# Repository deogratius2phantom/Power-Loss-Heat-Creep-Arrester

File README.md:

# Power Loss Heat Creep Arrester

A KiCad PCB design for a timer circuit that provides **24 V backup power to a 3D printer hotend fan** in the event of a power loss during printing. This prevents heat creep — the condition where residual heat travels up into the heatsink passage, causing filament to swell, clog, or jam.

---

## Overview

When a 3D printer loses power mid-print, the hotend heater turns off but residual heat remains in the heater block. Without the cooling fan running, this heat can creep up the cold zone, softening and swelling the filament inside the heatsink passage. The result is a jam that requires manual disassembly to clear.

This circuit detects the power loss event and uses a backup energy source (e.g. a capacitor bank or small battery) to keep the hotend fan spinning for a timed period — long enough for the heat to dissipate safely.

---

## Features

- Detects main power loss and triggers a timed backup fan drive
- Designed to supply 24 V to a standard 3D printer part-cooling or hotend fan
- Powered by a **Nokia BL-5C 3.7 V Li-ion battery** — widely available, compact, and plug-in replaceable
- Compact PCB footprint suitable for mounting inside a printer enclosure
- Fully open hardware (CC0 1.0 Universal licence)

---

## Board Preview

**Front (component side)**

**Back — rev_1.0 silkscreen**

The back silkscreen includes:
- **XundaTech / Heat Creep Arrester V1.0** — product branding
- **QR code** — scan to open this GitHub repository directly from the physical board
- **Connector pinout labels** (`FAN 24V`, `FAN GND`, `TO`, `GND`) — printed next to J3 for field assembly without needing a datasheet

📄 Full schematic & layout documentation: [PowerLossHeatCreepArrester.pdf](docs/PowerLossHeatCreepArrester.pdf)

---

## Repository Structure

```
Power-Loss-Heat-Creep-Arrester/
├── PowerLossHeatCreepArrester_v1.0/                      # KiCad v1.0 project (main design)
│   ├── PowerLossHeatCreepArrester_v1.0.kicad_pro         # KiCad project file
│   ├── PowerLossHeatCreepArrester_v1.0.kicad_sch         # Schematic
│   ├── PowerLossHeatCreepArrester_v1.0.kicad_pcb         # PCB layout
│   ├── board_v1.step                                     # 3D board export (v1)
│   ├── board_v11.step                                    # 3D board export (v11)
│   ├── .step                                             # Additional 3D export
│   ├── fabrication-toolkit-options.json                  # KiCad fabrication toolkit config
│   ├── bom/                                              # Bill of Materials & assembly aids
│   │   └── manual_assembly_ibom.html                    # Interactive BOM for manual assembly
│   └── production/                                       # Ready-to-order production files
│       ├── PowerLossHeatCreepArrester_v1.0.zip           # Gerber bundle for PCB fab
│       ├── bom.csv                                       # Bill of Materials
│       ├── designators.csv                               # Component designators
│       ├── netlist.ipc                                   # IPC netlist
│       └── positions.csv                                 # Pick-and-place positions
├── libraries/
│   └── PowerLossHeatCreepArrester.kicad_sym              # Custom schematic symbols
├── footprints/
│   └── PowerLossHeatCreepArrester.pretty/                # Custom PCB footprints
├── fabrication/
│   ├── gerbers/                                          # Gerber files for PCB manufacture
│   └── bom/                                             # Bill of Materials exports
├── docs/                                                 # Documentation & board images
│   ├── PowerLossHeatCreepArrester.pdf                   # Full schematic & layout PDF
│   ├── Screenshot 2026-06-02 at 18.37.28.png            # Board front view
│   └── Screenshot 2026-06-02 at 18.37.43.png            # Board back view
├── Heat Creep Arrester.pdf                               # Project overview document
├── .gitignore
├── LICENSE
└── README.md
```

---

## Getting Started

### Prerequisites

- [KiCad 7 or later](https://www.kicad.org/download/) (the project files use the KiCad 6+ S-expression format)

### Opening the Project

1. Clone or download this repository.
2. Open KiCad and select **File → Open Project**.
3. Navigate to `PowerLossHeatCreepArrester_v1.0/` and open `PowerLossHeatCreepArrester_v1.0.kicad_pro`.
4. The schematic (`*.kicad_sch`) and PCB layout (`*.kicad_pcb`) will be available from the KiCad project manager.

### Generating Fabrication Files

### Interactive BOM (Manual Assembly)

Open the interactive BOM directly in your browser — no setup needed:

**🔗 [View Interactive BOM online](https://htmlpreview.github.io/?https://github.com/deogratius2phantom/Power-Loss-Heat-Creep-Arrester/blob/main/PowerLossHeatCreepArrester_v1.0/bom/manual_assembly_ibom.html)**

Or open the file locally: `PowerLossHeatCreepArrester_v1.0/bom/manual_assembly_ibom.html`

It provides an interactive board view where you can click each component to highlight its placement — ideal for hand-soldering.

### Production Files

Ready-to-order files are in `PowerLossHeatCreepArrester_v1.0/production/`:

| File | Description |
|------|-------------|
| `PowerLossHeatCreepArrester_v1.0.zip` | Gerber bundle — upload directly to your PCB fab |
| `bom.csv` | Bill of Materials |
| `designators.csv` | Component designator mapping |
| `netlist.ipc` | IPC-D-356 netlist |
| `positions.csv` | Pick-and-place positions for SMT assembly |

To regenerate from source in KiCad PCB Editor (`pcbnew`):

1. Go to **File → Fabrication Outputs → Gerbers** → output to `fabrication/gerbers/`.
2. Generate the drill file via **File → Fabrication Outputs → Drill Files**.
3. Export the BOM via **File → Fabrication Outputs → BOM** → output to `fabrication/bom/`.

---

## Design Notes

| Parameter | Value |
|-----------|-------|
| Supply voltage | 24 V |
| Target load | Hotend / part-cooling fan |
| Fan activation | Only when hotend > 50 °C (adjustable via RV1) |
| Temperature sensing | Independent thermistor circuit (U4) — separate from printer NTC |
| PCB layers | 2 |
| Board thickness | 1.6 mm |
| Solder mask clearance | 0.005 mm |

---

## Revision History

### rev_1.0 (current branch)

Key changes from initial commit:

- **Independent temperature monitoring (U4 added):** A dedicated temperature sensing IC with its own thermistor was added after determining it is not feasible to share the printer's NTC across both the printer control board and this backup supply board without a carefully designed 3.3 V interface. U4 provides a clean, isolated temperature signal to LM393 comparator 2.
- **Comparator voltage divider recalculated:** R15 `210k → 52.3k`, R16 `40.2k → 10k` — revised to correctly set the 24 V power-loss detection threshold.
- **Hysteresis / reference network updated:** R21 `200k → 100k`, plus two comparator reference resistors adjusted (`10k → 47k` and `10k → 910k`) to match the new divider ratios.
- **GND symbol rerouted and thermistor label repositioned** on the schematic for clarity.
- **Net label typo fixed:** `indipendent_3d printer fan control input` → `independent_3d printer fan control input`.
- **PCB layout updated:** U4 placed at (138.51, 88.06), net assignments updated to match schematic changes, solder mask clearance set to 0.005 mm.
- **Back silkscreen additions:**
  - Product branding: `XundaTech / Heat Creep Arrester V1.0`
  - QR code linking to this GitHub repository (centre-back)
  - Connector pinout labels beside J3: `FAN 24V`, `FAN GND`, `TO`, `GND`

---

## Documentation

Full project documentation is in the [**GitHub Wiki**](https://github.com/deogratius2phantom/Power-Loss-Heat-Creep-Arrester/wiki):

| Wiki Page | Contents |
|-----------|----------|
| [Design Rationale](https://github.com/deogratius2phantom/Power-Loss-Heat-Creep-Arrester/wiki/Design-Rationale) | Why BL-5C, MT3608, TP4056, LM393 were chosen |
| [Circuit Theory](https://github.com/deogratius2phantom/Power-Loss-Heat-Creep-Arrester/wiki/Circuit-Theory) | How each circuit block works |
| [Bill of Materials & Sourcing](https://github.com/deogratius2phantom/Power-Loss-Heat-Creep-Arrester/wiki/Bill-of-Materials-and-Sourcing) | Full component list with supplier links |
| [Assembly Guide](https://github.com/deogratius2phantom/Power-Loss-Heat-Creep-Arrester/wiki/Assembly-Guide) | Step-by-step soldering instructions |
| [Testing & Calibration](https://github.com/deogratius2phantom/Power-Loss-Heat-Creep-Arrester/wiki/Testing-and-Calibration) | Verifying and tuning the circuit |
| [Troubleshooting](https://github.com/deogratius2phantom/Power-Loss-Heat-Creep-Arrester/wiki/Troubleshooting) | Common issues and fixes |
| [Version History](https://github.com/deogratius2phantom/Power-Loss-Heat-Creep-Arrester/wiki/Version-History) | Board revision log |

---

## Contributing

Contributions are welcome. See the [Contributing wiki page](https://github.com/deogratius2phantom/Power-Loss-Heat-Creep-Arrester/wiki/Contributing) for the full workflow. Please open an issue to discuss changes before submitting a pull request.

---

## Licence

This project is released into the public domain under the [CC0 1.0 Universal](LICENSE) licence. You are free to use, modify, and distribute this design without restriction.

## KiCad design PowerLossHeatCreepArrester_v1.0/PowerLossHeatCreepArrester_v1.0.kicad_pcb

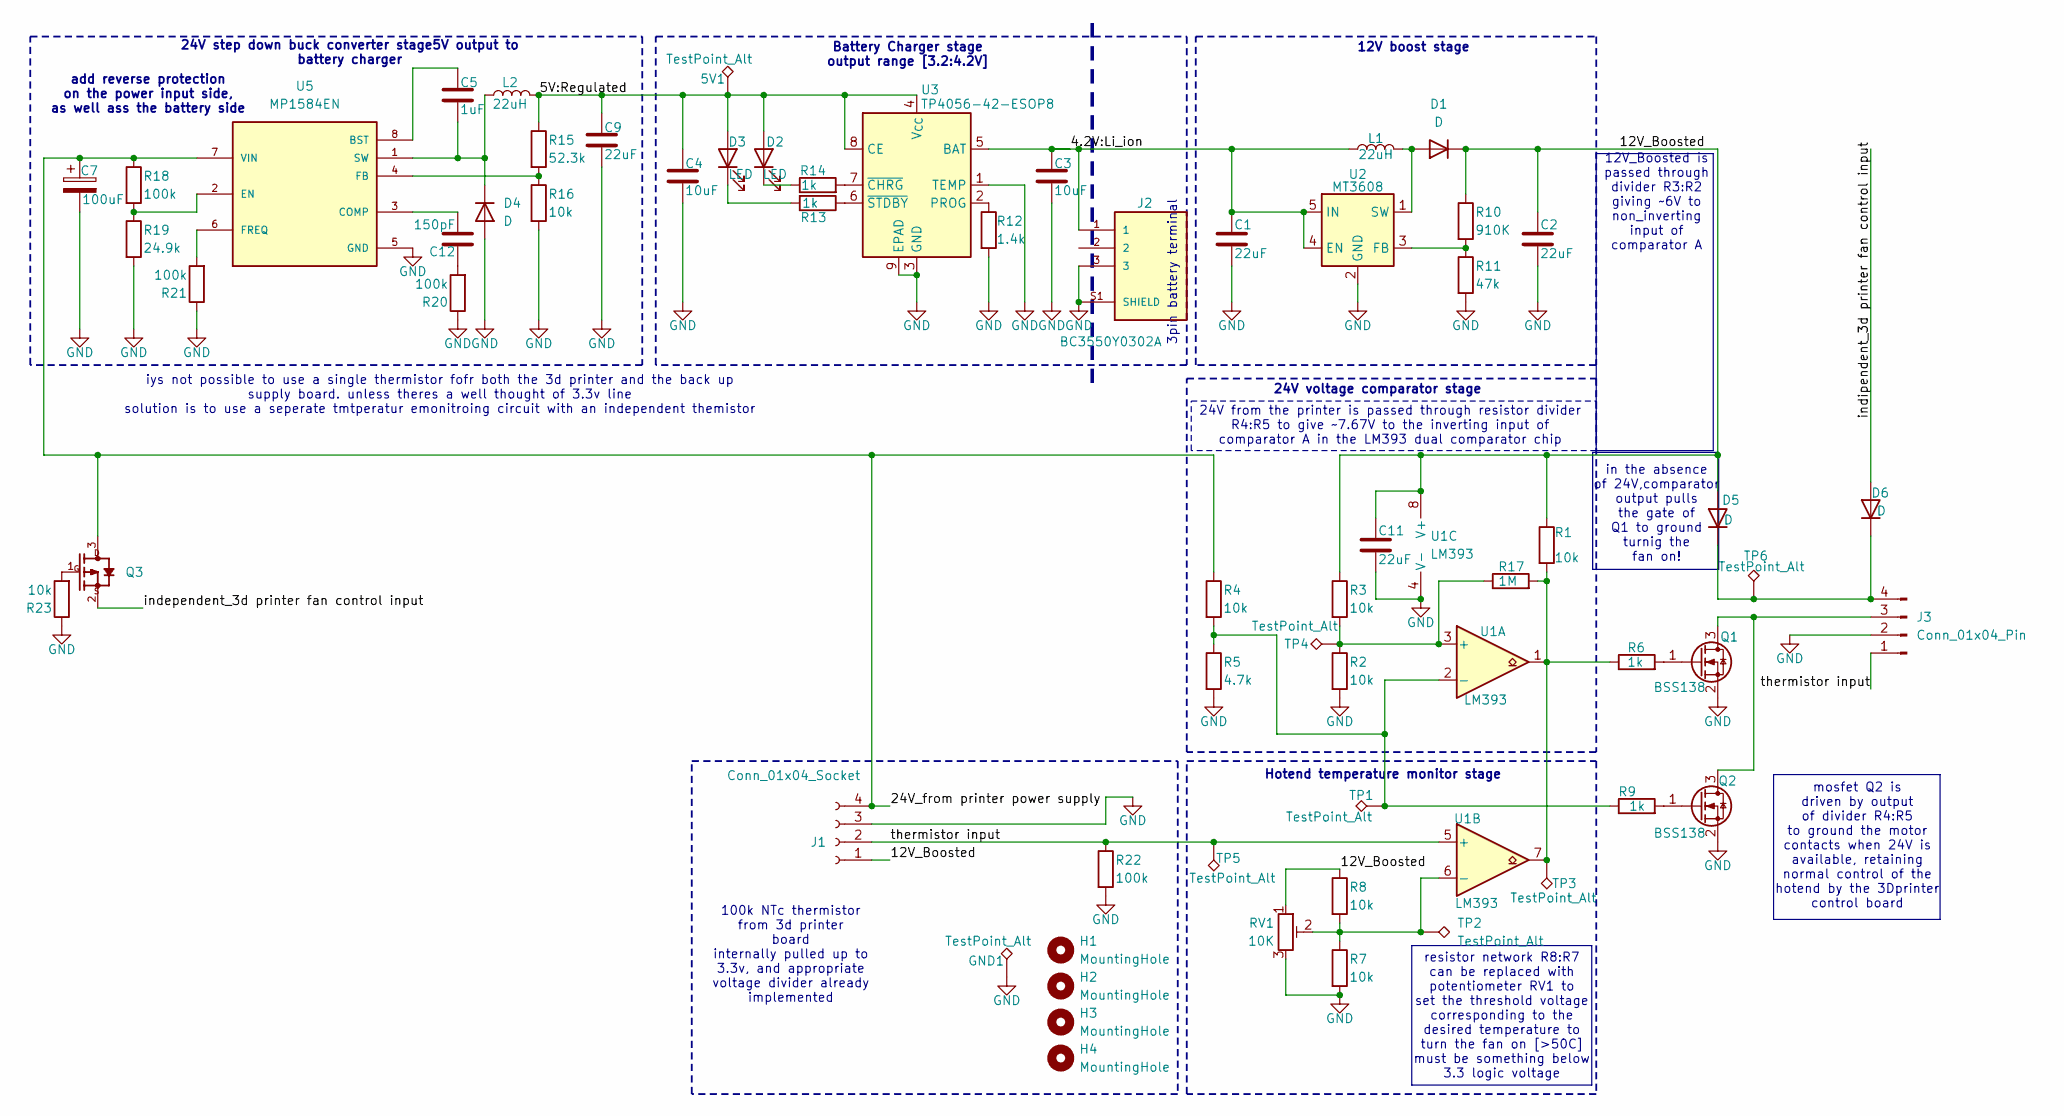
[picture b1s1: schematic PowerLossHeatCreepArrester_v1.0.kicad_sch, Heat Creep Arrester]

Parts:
5V1: TestPoint_Alt; TestPoint_Pad_D1.5mm
C1, C9: 22uF; C_0805_2012Metric
C2, C11: 22uF; C_0603_1608Metric
C3, C4: 10uF; C_0805_2012Metric
C5: 1uF; C_0805_2012Metric
C7: 100uF; CP_Radial_D5.0mm_P2.50mm
C12: 150pF; C_0603_1608Metric
D1, D4, D5, D6: D; D_SMA
D2, D3: LED; LED_0603_1608Metric
GND1: TestPoint_Alt; TestPoint_Pad_D1.5mm
H1, H2, H3, H4: MountingHole; MountingHole_3.2mm_M3_Pad
J1: Conn_01x04_Socket; PinHeader_1x04_P2.54mm_Vertical
J2: BC3550Y0302A; AMPHENOL_BC3550Y0302A; PARTREV 4
J3: Conn_01x04_Pin; PinHeader_1x04_P2.54mm_Vertical
L1, L2: 22uH; L_10.4x10.4_H4.8
Q1, Q2: BSS138; SOT-23
Q3: ZXMP6A13FTA; SOT-23; MPN ZXMP6A13FTA
R1, R2, R3, R4, R7, R8, R16, R23: 10k; R_0603_1608Metric
R5: 4.7k; R_0603_1608Metric
R6, R9, R13, R14: 1k; R_0603_1608Metric
R10: 910K; R_0603_1608Metric
R11: 47k; R_0603_1608Metric
R12: 1.4k; R_0603_1608Metric
R15: 52.3k; R_0603_1608Metric
R17: 1M; R_0603_1608Metric
R18, R20, R21, R22: 100k; R_0603_1608Metric
R19: 24.9k; R_0603_1608Metric
RV1: 10K; Potentiometer_ACP_CA14-VSMD_Vertical
TP1, TP2, TP3, TP4, TP5, TP6: TestPoint_Alt; TestPoint_Pad_D1.5mm
U1: LM393; SOIC-8_3.9x4.9mm_P1.27mm
U2: MT3608; SOT-23-6
U3: TP4056-42-ESOP8; SOIC-8-1EP_3.9x4.9mm_P1.27mm_EP2.41x3.3mm_ThermalVias
U5: MP1584EN; SOIC127P600X170-9N

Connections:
/4.2V:Li_ion: C1.1, C3.1, J2.1, L1.1, U2.4 (EN), U2.5 (IN), U3.5 (BAT)
/5V:Regulated: 5V1.1 (1_1), C4.1, C9.1, D2.2 (A), D3.2 (A), L2.2, R15.1, U3.4 (V_{CC}), U3.8 (CE)
/12V_Boosted: C2.1, C11.1, D1.1 (K), D5.2 (A), J1.1, R1.1, R3.1, R8.1, R10.1, RV1.1, U1.8 (V+)
/24V_from printer power supply: C7.1, J1.4, Q3.3, R4.1, R18.1, U5.7 (VIN)
/indipendent_3d printer fan control input: D6.2 (A)
/thermistor input: J1.2, J3.1, R22.1, TP5.1 (1_1), U1.5 (+)
GND: C1.2, C2.2, C3.2, C4.2, C7.2, C9.2, C11.2, D4.2 (A), GND1.1 (1_1), J1.3, J2.3, J2.S1 (SHIELD), J3.2, Q1.2 (S), Q2.2 (S), R2.2, R5.2, R7.2, R11.2, R12.2, R16.2, R19.2, R20.1, R21.1, R22.2, R23.1, RV1.3, U1.4 (V-), U2.2 (GND), U3.1 (TEMP), U3.3 (GND), U3.9 (EPAD), U5.5 (GND), U5.9 (GND)
unnamed: C12.1, R20.2
unnamed: D1.2 (A), L1.2, U2.1 (SW)
unnamed: D2.1 (K), R14.1
unnamed: D3.1 (K), R13.2
unnamed: C5.2, D4.1 (K), L2.1, U5.1 (SW)
unnamed: D5.1 (K), D6.1 (K), J3.4, TP6.1 (1_1)
unnamed: J3.3, Q1.3 (D), Q2.3 (D)
unnamed: Q1.1 (G), R6.2
unnamed: Q2.1 (G), R9.2
unnamed: Q3.1, R23.2
unnamed: R1.2, R6.1, R17.2, TP3.1 (1_1), U1.1, U1.7
unnamed: R2.1, R3.2, R17.1, TP4.1 (1_1), U1.3 (+)
unnamed: R4.2, R5.1, R9.1, TP1.1 (1_1), U1.2 (-)
unnamed: R7.1, R8.2, RV1.2, TP2.1, U1.6 (-)
unnamed: R10.2, R11.1, U2.3 (FB)
unnamed: R12.1, U3.2 (PROG)
unnamed: R14.2, U3.7 (~CHRG)
unnamed: R13.1, U3.6 (~STDBY)
unnamed: C5.1, U5.8 (BST)
unnamed: C12.2, U5.3 (COMP)
unnamed: R18.2, R19.1, U5.2 (EN)
unnamed: R15.2, R16.1, U5.4 (FB)
unnamed: R21.2, U5.6 (FREQ)

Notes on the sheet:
24V from the printer is passed through resistor divider R4:R5 to give ~7.67V to the inverting input of comparator A in the LM393 dual comparator chip
24V voltage comparator stage
Hotend temperature monitor stage
iys not possible to use a single thermistor fofr both the 3d printer and the back up supply board. unless theres a well thought of 3.3v line solution is to use a seperate tmtperatur emonitroing circuit with an independent themistor
add reverse protection on the power input side, as well ass the battery side
3pin battery terminal
Battery Charger stage output range [3.2:4.2V]
in the absence of 24V,comparator output pulls the gate of Q1 to ground turnig the fan on!
100k NTc thermistor from 3d printer board internally pulled up to 3.3v, and appropriate voltage divider already implemented
12V boost stage
resistor network R8:R7 can be replaced with potentiometer RV1 to set the threshold voltage corresponding to the desired temperature to turn the fan on [>50C] must be something below 3.3 logic voltage
12V_Boosted is passed through divider R3:R2 giving ~6V to non_inverting input of comparator A
24V step down buck converter stage5V output to battery charger
mosfet Q2 is driven by output of divider R4:R5 to ground the motor contacts when 24V is available, retaining normal control of the hotend by the 3Dprinter control board

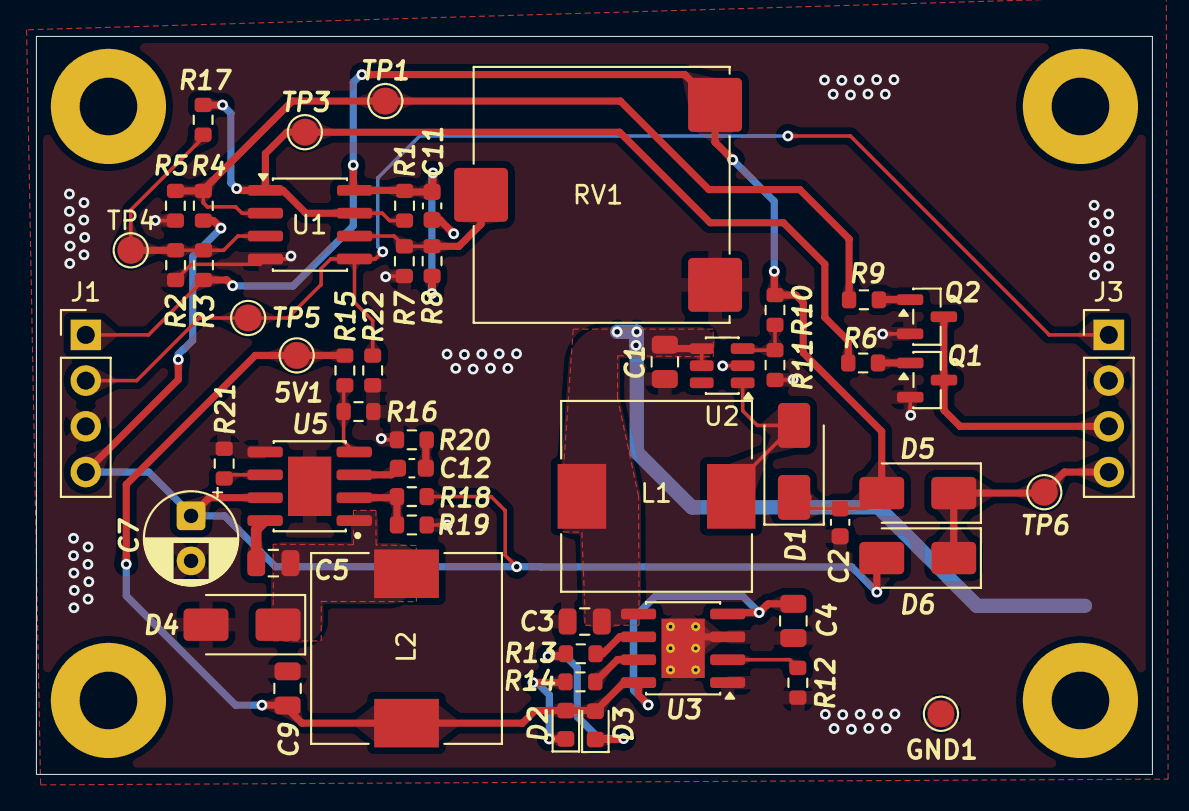
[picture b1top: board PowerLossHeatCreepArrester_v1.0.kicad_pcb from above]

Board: 2 copper layers, 62.0 x 41.0 mm, 60 parts (1 on the bottom side), 28 nets.

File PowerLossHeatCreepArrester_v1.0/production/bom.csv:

Designator,Footprint,Quantity,Value,LCSC Part #
"C1, C9",0805,2,22uF,
"C11, C2",0603,2,22uF,
C12,0603,1,150pF,
"C3, C4",0805,2,10uF,
C5,0805,1,1uF,
C7,CP_Radial_D5.0mm_P2.50mm,1,100uF,
"D1, D4, D5, D6",D_SMA,4,D,
"D2, D3",0603,2,LED,
J1,PinHeader_1x04_P2.54mm_Vertical,1,Conn_01x04_Socket,
J2,AMPHENOL_BC3550Y0302A,1,BC3550Y0302A,
J3,PinHeader_1x04_P2.54mm_Vertical,1,Conn_01x04_Pin,
"L1, L2",L_10.4x10.4_H4.8,2,22uH,
"Q1, Q2",SOT-23,2,BSS138,
"R1, R10, R11, R2, R3, R4, R7, R8",0603,8,10k,
R12,0603,1,1.4k,
"R13, R14, R6, R9",0603,4,1k,
R15,0603,1,210k,
R16,0603,1,40.2k,
R17,0603,1,1M,
"R18, R20",0603,2,100k,
R19,0603,1,24.9k,
R21,0603,1,200k,
R5,0603,1,4.7k,
RV1,Potentiometer_ACP_CA14-VSMD_Vertical,1,10K,
"TP1, TP3, TP4, TP5, TP6",TestPoint_Pad_D1.5mm,5,TestPoint_Alt,
U1,SOIC-8_3.9x4.9mm_P1.27mm,1,LM393,
U2,SOT-23-6,1,MT3608,
U3,SOIC-8-1EP_3.9x4.9mm_P1.27mm_EP2.41x3.3mm_ThermalVias,1,TP4056-42-ESOP8,
U5,SOIC127P600X170-9N,1,MP1584EN,

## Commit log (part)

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2026-03-14 Initial plan
2026-03-14 Configure KiCad PCB project structure with appropriate README
